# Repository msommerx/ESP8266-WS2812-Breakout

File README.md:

# ESP8266-WS2812-Breakout
Small Breakoutboard to controll WS2812 LEDs with ESP8266.

ESP8266 needs to be programmed before soldered.

+5 V Input with reverse polarity protection. 
Do not short AGND and GND.

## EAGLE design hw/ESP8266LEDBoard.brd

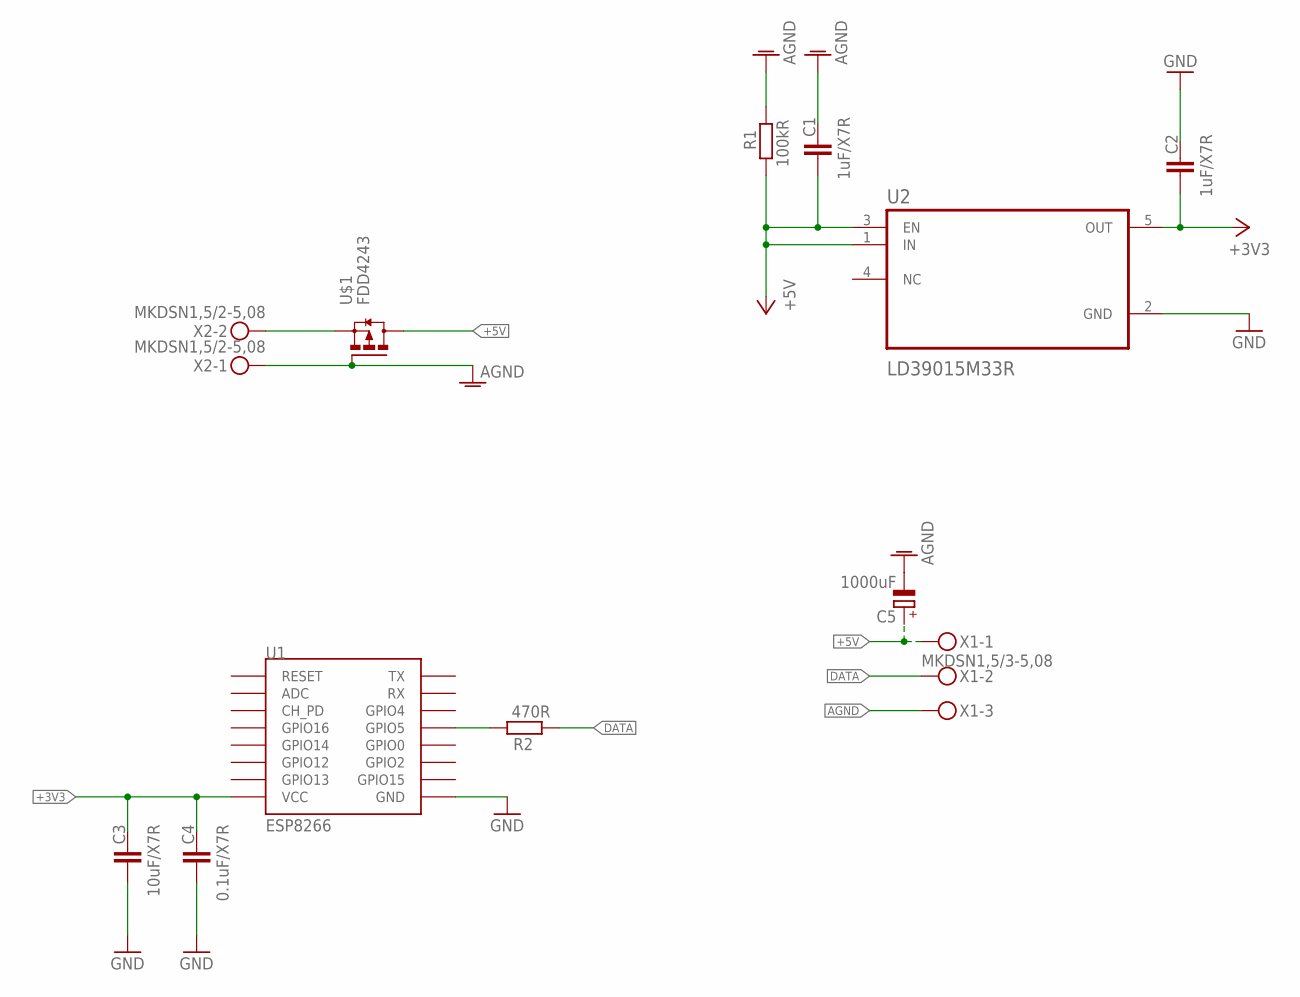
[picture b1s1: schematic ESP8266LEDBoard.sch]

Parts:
C1, C2: 1uF/X7R; C0805
C3: 10uF/X7R; C0805
C4: 0.1uF/X7R; C0805
C5: 1000uF; UD-8X10_NICHICON
R1: 100kR; R0805
R2: 470R; R0805
U1: ESP8266; ESP12-SMD
U2: LD39015M33R; SOT95P280X145-5N
U$1: FDD4243; TO252
X1: MKDSN1,5/3-5,08
X2: MKDSN1,5/2-5,08

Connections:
+3V3: C2.1, C3.2, C4.2, U1.VCC, U2.5 (OUT)
+5V: C1.1, C5.+, R1.1, U2.1 (IN), U2.3 (EN), U$1.3 (D), X1.1
AGND: C1.2, C5.-, R1.2, U$1.1 (G), X1.3, X2.1
DATA: R2.1, X1.2
GND: C2.2, C3.1, C4.1, U1.GND, U2.2 (GND)
unnamed: U$1.2 (S), X2.2
unnamed: R2.2, U1.GPIO5

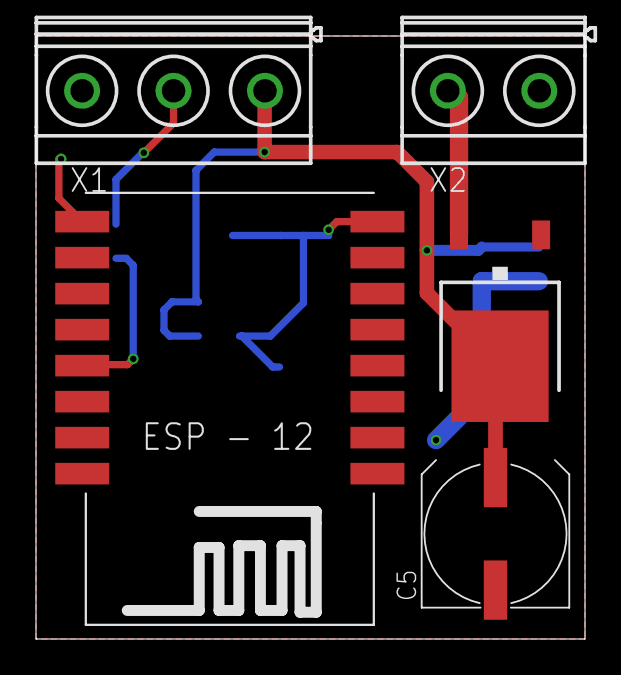
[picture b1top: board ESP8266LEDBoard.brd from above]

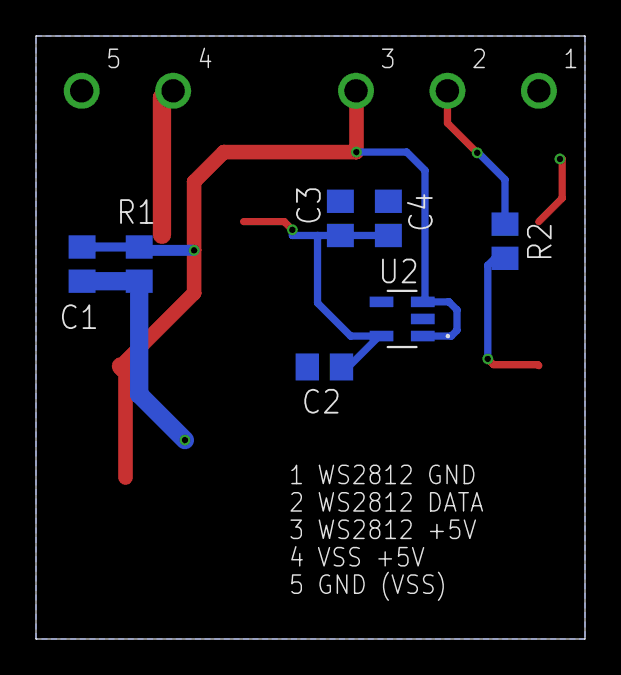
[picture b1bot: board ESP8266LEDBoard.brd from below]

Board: 2 copper layers, 30.5 x 33.5 mm, 12 parts (7 on the bottom side), 7 nets.

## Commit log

2019-01-04 Create hw
2019-01-04 folderstructure and eagle libs
